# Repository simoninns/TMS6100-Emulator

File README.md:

## Synopsis

TMS6100 speech PHROM (PHrase Read Only Memory) hardware emulator for use with the TMS5220 Voice Synthesis Processor in an Acorn BBC Microcomputer

## Motivation

This project creates a TMS6100 speech PHROM (PHrase Read Only Memory) for use with the TMS5220 Voice Synthesis Processor in an Acorn BBC Microcomputer. Whilst it’s still possible to purchase TMS5220 ICs from sites like Ebay, the TMS6100 was a mask-programmed ROM that Acorn produced specifically for their speech upgrade and is therefore difficult and expensive to source. Instead of using the original ROM, this project uses an ATmega32U2 microcontroller to both emulate the ROM and provide the original Acorn voice sample data recorded by BBC newsreader Kenneth Kendall.

## Installation

Note: This is an Atmel Studio 7 project that can be loaded and compiled by the IDE

Please see http://www.waitingforfriday.com/?p=30 for detailed documentation about TMS6100-Emulator

The PHROM data for both the Acorn Speech System PHROM and the American TI PHROM is included in the source-code.  By default it will compile using the Acorn Speech Data.  Specifying the compiler macro PHROM_ACORN selects the Acorn PHROM and PHROM_US selects the American PHROM.  Note that the American PHROM is not generally for use with the BBC Micro and is included for experimental use (or use in other microcomputer systems).

## Author

TMS6100-Emulator is written and maintained by Simon Inns.

## License (Software)

    TMS6100-Emulator is free software: you can redistribute it and/or modify
    it under the terms of the GNU General Public License as published by
    the Free Software Foundation, either version 3 of the License, or
    (at your option) any later version.

    TMS6100-Emulator is distributed in the hope that it will be useful,
    but WITHOUT ANY WARRANTY; without even the implied warranty of
    MERCHANTABILITY or FITNESS FOR A PARTICULAR PURPOSE.  See the
    GNU General Public License for more details.

    You should have received a copy of the GNU General Public License
    along with TMS6100-Emulator. If not, see <http://www.gnu.org/licenses/>.

## License (Hardware)

Both the schematic and the PCB design of TMS6100-Emulator are covered by a Creative Commons license; as with the software you are welcome (and encouraged!) to extend, re-spin and otherwise use and modify the design as allowed by the license.  However; under the terms of the Attribution-ShareAlike 4.0 International (CC BY-SA 4.0) license you are required to release your design (or redesign) under the same license.  For details of the licensing requirements please see <https://creativecommons.org/licenses/by-sa/4.0/>

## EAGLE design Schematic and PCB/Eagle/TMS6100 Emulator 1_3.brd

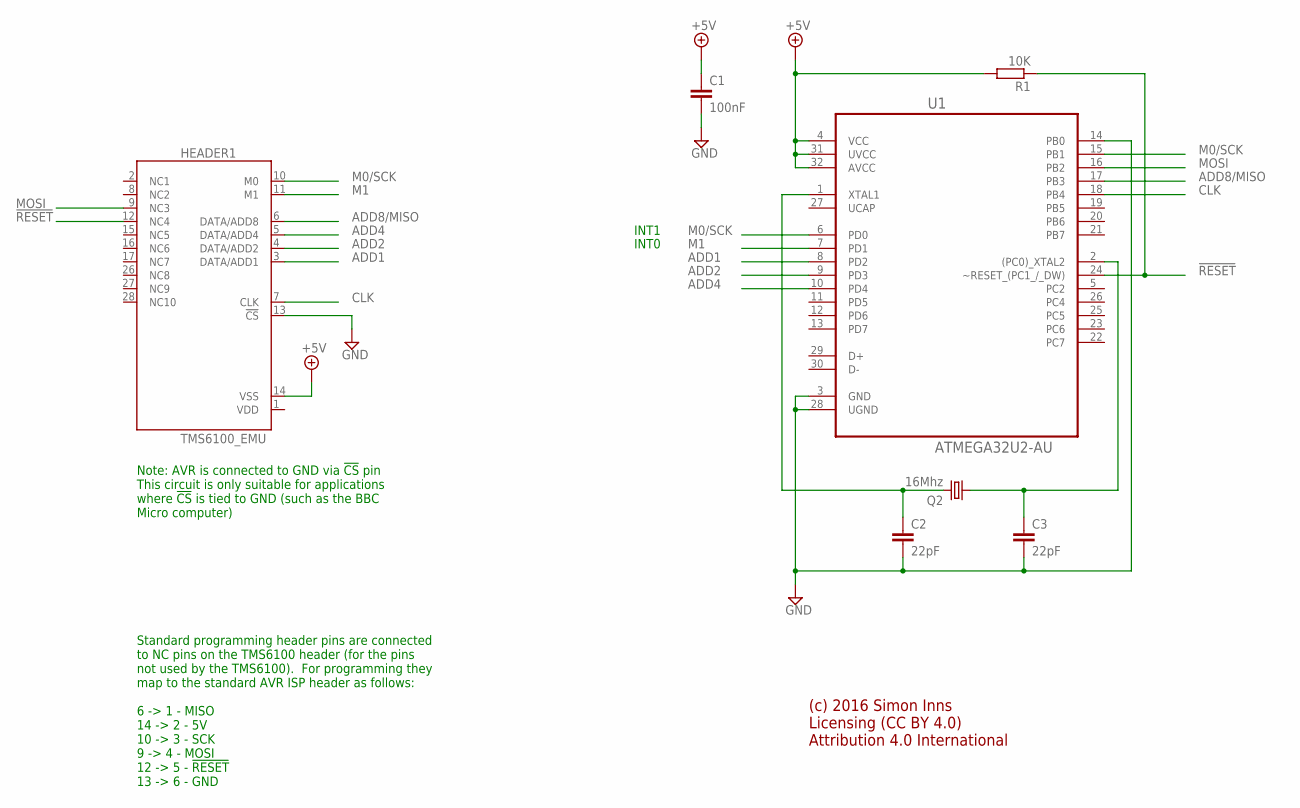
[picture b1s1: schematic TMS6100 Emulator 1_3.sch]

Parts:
C1: 100nF; C0805
C2, C3: 22pF; C0805
HEADER1: TMS6100_EMU; DIL28-6_TMS6100
Q2: 16Mhz; CRYSTAL_SMD_3X5MM
R1: 10K; R1206
U1: ATMEGA32U2-AU; QFP80P900X900X120-32N

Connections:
!RESET: HEADER1.12 (NC4), R1.1, U1.24 (~RESET_(PC1_/_DW))
+5V: C1.1, HEADER1.14 (VSS), R1.2, U1.4 (VCC), U1.31 (UVCC), U1.32 (AVCC)
ADD1: HEADER1.3 (DATA/ADD1), U1.8 (PD2)
ADD2: HEADER1.4 (DATA/ADD2), U1.9 (PD3)
ADD4: HEADER1.5 (DATA/ADD4), U1.10 (PD4)
ADD8/MISO: HEADER1.6 (DATA/ADD8), U1.17 (PB3)
CLK: HEADER1.7 (CLK), U1.18 (PB4)
GND: C1.2, C2.2, C3.2, HEADER1.13 (!CS), U1.3 (GND), U1.14 (PB0), U1.28 (UGND)
M0/SCK: HEADER1.10 (M0), U1.6 (PD0), U1.15 (PB1)
M1: HEADER1.11 (M1), U1.7 (PD1)
MOSI: HEADER1.9 (NC3), U1.16 (PB2)
unnamed: C2.1, Q2.2, U1.1 (XTAL1)
unnamed: C3.1, Q2.1, U1.2 ((PC0)_XTAL2)
UCAP: U1.27 (UCAP)
VDD: HEADER1.1 (VDD)

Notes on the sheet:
(c) 2016 Simon Inns Licensing (CC BY 4.0) Attribution 4.0 International
Note: AVR is connected to GND via !CS! pin This circuit is only suitable for applications where !CS! is tied to GND (such as the BBC Micro computer)
Standard programming header pins are connected to NC pins on the TMS6100 header (for the pins not used by the TMS6100). For programming they map to the standard AVR ISP header as follows: 6 -> 1 - MISO 14 -> 2 - 5V 10 -> 3 - SCK 9 -> 4 - MOSI 12 -> 5 - !RESET 13 -> 6 - GND
INT0
INT1

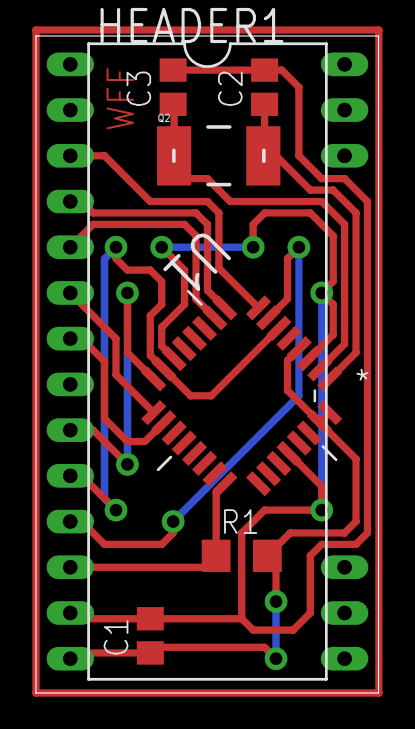
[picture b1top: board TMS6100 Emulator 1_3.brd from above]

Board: 2 copper layers, 19.0 x 36.5 mm, 7 parts (0 on the bottom side), 13 nets.

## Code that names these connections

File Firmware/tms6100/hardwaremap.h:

/************************************************************************
	hardwaremap.h

    Physical hardware mapping definitions for portability
    Copyright (C) 2018 Simon Inns

    This file is part of the TMS6100-Emulator.

    The TMS6100-Emulator is free software: you can
    redistribute it and/or modify it under the terms of the GNU
    General Public License as published by the Free Software
    Foundation, either version 3 of the License, or (at your
    option) any later version.

    This program is distributed in the hope that it will be useful,
    but WITHOUT ANY WARRANTY; without even the implied warranty of
    MERCHANTABILITY or FITNESS FOR A PARTICULAR PURPOSE.  See the
    GNU General Public License for more details.

    You should have received a copy of the GNU General Public License
    along with this program.  If not, see <http://www.gnu.org/licenses/>.

    Email: simon.inns@gmail.com

    ************************************************************************/

#ifndef HARDWAREMAP_H_
#define HARDWAREMAP_H_

// Target device: ATmega32u2
// Also tested on the ATmega32u4 (Arduino Leonardo mini pro)

// Definitions for TMS6100 IO Pins --------------------------------------

// ADD1 (PD2)
#define TMS6100_ADD1_PORT	PORTD
#define TMS6100_ADD1_PIN	PIND
#define TMS6100_ADD1_DDR	DDRD
#define TMS6100_ADD1		(1 << 2)

// ADD2 (PD3)
#define TMS6100_ADD2_PORT	PORTD
#define TMS6100_ADD2_PIN	PIND
#define TMS6100_ADD2_DDR	DDRD
#define TMS6100_ADD2		(1 << 3)

// ADD4 (PD4)
#define TMS6100_ADD4_PORT	PORTD
#define TMS6100_ADD4_PIN	PIND
#define TMS6100_ADD4_DDR	DDRD
#define TMS6100_ADD4		(1 << 4)

// ADD8 (PB3/MOSI)
#define TMS6100_ADD8_PORT	PORTB
#define TMS6100_ADD8_PIN	PINB
#define TMS6100_ADD8_DDR	DDRB
#define TMS6100_ADD8		(1 << 3)

// M0 (PD0/INT0)
#define TMS6100_M0_PORT		PORTD
#define TMS6100_M0_PIN		PIND
#define TMS6100_M0_DDR		DDRD
#define TMS6100_M0			(1 << 0)
#define TMS6100_M0_INT		INT0
#define TMS6100_M0_INT_VECT	INT0_vect
#define TMS6100_M0_ISC0		ISC00
#define TMS6100_M0_ISC1		ISC01
#define TMS6100_M0_INTF		INTF0

// M1 (PD1/INT1)
#define TMS6100_M1_PORT		PORTD
#define TMS6100_M1_PIN		PIND
#define TMS6100_M1_DDR		DDRD
#define TMS6100_M1			(1 << 1)
#define TMS6100_M1_INT		INT1
#define TMS6100_M1_INT_VECT	INT1_vect
#define TMS6100_M1_ISC0		ISC10
#define TMS6100_M1_ISC1		ISC11
#define TMS6100_M1_INTF		INTF1

// CLK (PB4) - Not currently used by the emulator as we use
// the SPI module to asynchronously time data based on the 
// M0 pulses (which has the effect of making the data in sync
// with the clock).
#define TMS6100_CLK_PORT	PORTB
#define TMS6100_CLK_PIN		PINB
#define TMS6100_CLK_DDR		DDRB
#define TMS6100_CLK			(1 << 4)

// Definitions for SPI pins ---------------------------------------------

// MISO - This is ADD8 defined above 

// MOSI (PB2)
#define TMS6100_MOSI_PORT	PORTB
#define TMS6100_MOSI_PIN	PINB
#define TMS6100_MOSI_DDR	DDRB
#define TMS6100_MOSI		(1 << 2)

// SCK (PB1)
#define TMS6100_SCK_PORT	PORTB
#define TMS6100_SCK_PIN		PINB
#define TMS6100_SCK_DDR		DDRB
#define TMS6100_SCK			(1 << 1)

// !SS (PB0)
#define TMS6100_SS_PORT		PORTB
#define TMS6100_SS_PIN		PINB
#define TMS6100_SS_DDR		DDRB
#define TMS6100_SS			(1 << 0)

// Definitions for debug pins -------------------------------------------

// Note: These pins are used for development and are not present
// on the production version of the PCB

#define DEBUG0_PORT	PORTD
#define DEBUG0_PIN	PIND
#define DEBUG0_DDR	DDRD
#define DEBUG0		(1 << 5)

#define DEBUG1_PORT	PORTD
#define DEBUG1_PIN	PIND
#define DEBUG1_DDR	DDRD
#define DEBUG1		(1 << 6)

#define DEBUG2_PORT	PORTD
#define DEBUG2_PIN	PIND
#define DEBUG2_DDR	DDRD
#define DEBUG2		(1 << 7)

#endif /* HARDWAREMAP_H_ */

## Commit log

2018-04-10 Initial commit of project files (firmware and eagle cad)
2018-04-10 Corrected source files - fixed header information
2018-04-10 kicad schematics
2018-04-10 Updated schematic and included fixes
    I've modified the labels into global labels and corrected PB0. Components and nodes have been space out to make the diagram clearer. Power connections are now pointing in the correct directions. Also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
2018-04-12 Fix ERC, also socket
2018-04-12 Correct component for socket, footprints mapped
2018-04-14 V1 PCB Layout
2018-04-14 Silkscreen fixed
2018-04-14 Vias fixed
2018-04-14 reverse ground plane added
2018-04-15 Additional changes to schematic and PCB
    Added 'R' to 330R resistor
    Added PCB edge cuts and rearranged text markers into boundaries
    Orientated resistors the same for quicker assembly
    Added URL for WFF
    Added additional marker for TQPF visual orientation
    Removed unnecessary vias around reset pull up resistor
2018-04-15 Added gerbers and PDF files, removed Eagle files
2018-05-01 Added CC license to KiCAD files
2018-05-07 Fixed issue where fuse setting prevented emulator from functioning
    Added override for WDT and clock div 8 fuse settings (now works with stock ATmega32u2 without the need to reprogram fuses).
    Also fixed build environment to compile in release mode rather than debug (with -O1 optimisation).
2018-05-10 Added American PHROM speech data and compiler directives to select required image.
    Specifying -DPHROM_ACORN will compile the Acorn Speech System PHROM data (default) and specifying -DPHROM_US will compile the US speech PHROM data.
2018-06-15 Added support for PHROM bank number
    The emulator now honours the PHROM bank number meaning that, on a BBC Micro SOUND -1, x, 0, 0 will address the Acorn PHROM and SOUND -16, x, 0, 0 will access the US PHROM. Address incrementation has 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
    Note that 'stacking' of PHROMs will not currenly work as the emulator's pins are not passive when another bank is selected.
2018-06-17 Removed SPI, replaced with bit-banging method
    The use of the SPI module has been removed to allow better control over the READ DATA command signals. The READ DATA command is now performed purely using interrupts on the M0 signal.
2018-06-17 Added code to float ADD8 when PHROM's bank isn't selected. Code currently shows timing issues
    READ DATA command is not currently 100% successful. Emulator is causing sample corruption.
2018-06-17 Removed Interrupt Service Requests to improve response speeds
2018-06-17 Non-functioning build - access time from M0 control still to slow (needs to be <2us)
2018-06-17 Revert "Non-functioning build - access time from M0 control still to slow (needs to be <2us)"
    This reverts commit 3a050840b85f405825ca27e36f8b6f29d2051f4c.
2018-06-17 Added back in SPI code - timing of data output on ADD8 is not correct
    The timing possible without using SPI is not fast enough for the primary transfer. Remerging SPI code. Idea will be to use SPI when bank is valid and then use interrupts to track M0 during non-local 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
2018-06-18 Interim check in with SPI re-enabled
    Not currently working; first read data is missing a leading 0
2018-06-23 Better logic trace comparison to original PHROM, but still non-functional
2018-06-28 New working version without interrupts or SPI - with more accurate timing
2018-06-28 Emulator now correctly supports 'stacked' PHROMs allowing multiple PHROMs to be used at once
2018-06-29 Minor clean-up of code
